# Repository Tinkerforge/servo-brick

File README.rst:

Servo Brick
===========

This repository contains the firmware source code and the hardware design
files. The documentation generator configs can be found at
https://github.com/Tinkerforge/generators

Repository Content
------------------

software/:
 * examples/: Examples for all supported languages
 * build/: Compiled files
 * src/: Source code of firmware
 * Makefile: Makefile to build project

hardware/:
 * Contains KiCad project files and additionally schematics as PDF

datasheets/:
 * Contains datasheets for sensors and complex ICs that are used

Hardware
--------

The hardware is designed with the open source EDA Suite KiCad
(http://www.kicad.org). Before you are able to open the files,
you have to install the Tinkerforge kicad-libraries
(https://github.com/Tinkerforge/kicad-libraries). You can either clone
them directly in hardware/ or clone them in a separate folder and
symlink them into hardware/
(ln -s kicad_path/kicad-libraries project_path/hardware). After that you
can open the .pro file in hardware/ with KiCad and from there view and
modify the schematics and the PCB layout.

Software
--------

If you want to do your own Brick/Bricklet firmware development we highly
recommend that you use our build environment setup script and read the
tutorial (https://www.tinkerforge.com/en/doc/Tutorials/Tutorial_Build_Environment/Tutorial.html).

To compile the C code we recommend you to install the newest GNU Arm Embedded
Toolchain (https://launchpad.net/gcc-arm-embedded/+download).
You also need to install bricklib (https://github.com/Tinkerforge/bricklib).

You can either clone it directly in software/src/ or clone it in a
separate folder and symlink it into software/src/
(ln -s bricklib_path/bricklib project_path/software/src/). Finally make sure to
have CMake installed (http://www.cmake.org/cmake/resources/software.html).

After that you can build the firmware by invoking make in software/.
The firmware (.bin) can then be found in software/build/ and uploaded
with brickv (click button "Flashing" on start screen).

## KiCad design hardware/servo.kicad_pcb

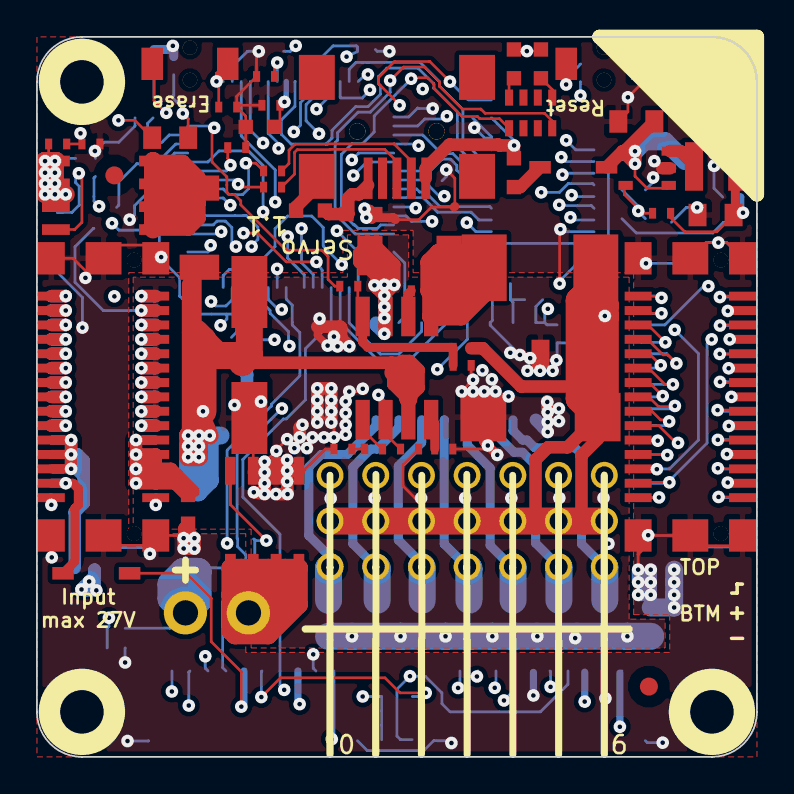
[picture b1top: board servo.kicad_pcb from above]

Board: 4 copper layers, 40.0 x 40.0 mm, 113 parts (0 on the bottom side), 116 nets.

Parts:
C1, C2: 9pF; C0402
C3: 100µF; 3528-21
C4, C6: 10µF; C0805
C5, C8, C9, C10, C12, C13, C15, C16, C18, C20, C21, C27, C28, C32: 100nF; C0402
C7, C19: 4.7µF; C0603
C11: 2.2µF; C0603
C14: DNP; C0402
C17: 10µF/10V; C0805
C22: 220µF/35V; ELKO_83
C23: 10µF/35V; C1206
C24, C30: 100nF; C0603
C25: 1µF/10V; C0402
C26: 1nF; C0402
C29: 1µF/10V; 0402
C31: 47µF/10V; C1206
C33: 470µF/10V; 7343
D1: blue; D0603
D2: red; D0603
D3, D5: B0520LW-7-F; SOD-123
D4: Z3.3V; SOD-123
D6: Z12V; SOD-123
D7, D8, D9: PMEG4050BEP; SOD-128
FB1, FB2, FB3, FB4, FB5: FB; C0603
Fiducial_Mark: VAL**; Fiducial_Mark
Fiducial_Mark#2, Fiducial_Mark#3, Fiducial_Mark#4: VAL**; Fiducial_Mark
J1, J2, J3, J4: DRILL; DRILL_NP
J5: USB-MINI-B-SMD
J6, J8: STACK-UP-HIGH; BTB08-ACS-TOP
J7, J9: STACK-DOWN; BTB08-ACS-BTM
J10: CON-SERVO; CON-Servo
L1: NR3015T4R7M; NR3030
L2: LBR2012T100K; C0805
L3: 10µH; SRP7030
P1, P2: CON-SENSOR
P3: black; OQ_2P
Q1: FDS8449; SOIC-8-MOSFET
Q2: AO4421; SOIC-8-MOSFET
Q3: 2N7002; SOT23GDS
R1, R2: 27; R0402
R3: 1.8k; R0402
R4: 2.7k; R0402
R5: 0; R0603
R6: DNP; R0603
R7: 1R0; R0402
R8, R11, R15, R18, R23: 1k; R0402
R9: FB; C0603
R10, R13, R14, R16, R17, R20, R21, R22: 10k; R0402
R12, R19: 100k; R0402
R24, R25, R26, R27, R28, R29, R30: 0R1; R0805
RP1, RP2: 1k; 4X0603
Ref**: Val**; Logo_31x31m
SW1: Reset; TACT-SWITCH
SW2: Erase; TACT-SWITCH
U1: AT91SAM3SXB; LQFP64
U2: EUP3406; SOT23-5
U3: AOZ1212; SO-8
U4: 74HC245; TSSOP20
U5: MCP3008; SOIC16
VAL: CE_5mm
VAL#2: WEEE_7mm
X1: 16Mhz; CRYSTAL_3225

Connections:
3V3: C4.1, C5.1, C7.1, C8.1, C9.1, C10.1, C14.1, C17.1, C18.1, C21.1, C29.1, D1.1, D2.1, D4.2, D5.1, J6.20, L1.2, P1.3, P1.6, P2.3, R5.1, R22.2, RP2.1, RP2.2, RP2.3, RP2.4, SW2.2, U1.1, U1.7, U1.18, U1.45, U1.58, U5.16
BRICKLET-I2C-SCL: P1.4, P2.4, RP2.5, U1.36
BRICKLET-I2C-SDA: P1.5, P2.5, RP2.8, U1.43
BRICKLET-IO0_0/AD0: P1.7, U1.3
BRICKLET-IO0_1/DA0: P1.8, U1.59
BRICKLET-IO0_2/PWM0: P1.9, U1.20
BRICKLET-IO0_3: P1.10, U1.41
BRICKLET-IO1_0/AD1: P2.7, U1.4
BRICKLET-IO1_1: P2.8, U1.6
BRICKLET-IO1_2/PWM1: P2.9, U1.42
BRICKLET-IO1_3: P2.10, U1.47
CUR-SERVO-0: J10.A1, R24.1, U5.8
CUR-SERVO-1: J10.B1, R25.1, U5.7
CUR-SERVO-2: J10.C1, R26.1, U5.6
CUR-SERVO-3: J10.D1, R27.1, U5.5
CUR-SERVO-4: J10.E1, R28.1, U5.4
CUR-SERVO-5: J10.F1, R29.1, U5.3
CUR-SERVO-6: J10.G1, R30.1, U5.2
GND: C1.2, C2.2, C3.2, C4.2, C5.2, C6.2, C7.2, C8.2, C9.2, C10.2, C11.2, C12.2, C13.2, C15.2, C16.2, C17.2, C18.2, C19.2, C20.2, C21.2, C32.2, D4.1, FB1.1, FB4.2, J6.EP, J7.EP, J8.EP, J9.EP, P1.2, P1.EP, P2.2, P2.6, P2.EP, R4.1, R6.2, R9.2, R11.1, R15.1, R18.1, SW1.2, U1.2, U1.17, U1.46, U1.60, U2.2, U4.9, U4.10, U4.19, X1.3
unnamed: C11.1, C12.1, C13.1, C15.1, C16.1, L2.1, U1.8, U1.12, U1.24, U1.54
unnamed: C14.2, R5.2, R6.1, U2.5
unnamed: C19.1, R7.1
unnamed: C20.1, L2.2, R7.2, U1.64
unnamed: C22.1, C23.1, C24.1, D7.2, D8.2, U3.7
unnamed: C25.1, U3.8
unnamed: C26.1, R17.1
unnamed: C27.1, D9.2, L3.1, U3.1
unnamed: C27.2, U3.2
unnamed: C28.2, R22.1, R23.2, U5.15
unnamed: D1.2, RP1.8
unnamed: D2.2, RP1.5
unnamed: D5.2, J8.28, J9.28
unnamed: D6.2, Q1.G, R12.2
unnamed: D7.1, P3.1, R12.1, R14.2
unnamed: D8.1, Q2.D
unnamed: FB1.2, FB2.1, J5.5
unnamed: FB2.2, J5.6
unnamed: FB3.2, J5.1, R3.1
unnamed: FB4.1, J8.21, J8.23, J8.25, J8.27, J9.21, J9.23, J9.25, J9.27
unnamed: FB5.2, J8.22, J8.24, J8.26, J9.22, J9.24, J9.26
unnamed: J5.2, R1.1
unnamed: J5.3, R2.1
unnamed: J6.6, J7.8
unnamed: J6.7, J7.7, R8.1
unnamed: J6.8, J7.10
unnamed: J6.10, J7.12
unnamed: J6.12, J7.14
unnamed: J6.13, J7.13
unnamed: J6.14, J7.16
unnamed: J6.15, J7.15
unnamed: J6.16, J7.18
unnamed: J6.17, J7.17
unnamed: J6.18, J7.20
unnamed: J6.21, J7.21
unnamed: J6.22, J7.22
unnamed: J6.23, J7.23
unnamed: J6.24, J7.24
unnamed: J6.25, J7.25
unnamed: J6.27, J7.27
unnamed: J6.29, J7.29
unnamed: J6.30, J7.30
unnamed: J8.29, J9.29
unnamed: J8.30, J9.30
unnamed: J10.A3, U4.12
unnamed: J10.B3, U4.13
unnamed: J10.C3, U4.14
unnamed: J10.D3, U4.15
unnamed: J10.E3, U4.16
unnamed: J10.F3, U4.17
unnamed: J10.G3, U4.18
unnamed: L1.1, U2.3
unnamed: P3.2, Q1.D
unnamed: Q2.G, Q3.D, R13.2
unnamed: R1.2, U1.56
unnamed: R2.2, U1.57
unnamed: R17.2, U3.5
unnamed: R19.2, R20.1, R21.2, U3.4
unnamed: RP1.1, U1.30
unnamed: RP1.4, U1.29
unnamed: SW2.1, U1.55
PWM-SERVO-0: U1.48, U4.2
PWM-SERVO-1: U1.26, U4.3
PWM-SERVO-2: U1.25, U4.4
PWM-SERVO-3: U1.23, U4.5
PWM-SERVO-4: U1.19, U4.6
PWM-SERVO-5: U1.9, U4.7
PWM-SERVO-6: U1.15, U4.8
PWR-AD-CLK: U1.44, U5.13
PWR-AD-CS: U1.32, U5.10
PWR-AD-MISO: U1.35, U5.12
PWR-AD-MOSI: U1.34, U5.11
PWR-ENABLE: R16.2, U1.16, U3.6
PWR-SET-VOLTAGE: R21.1, U1.63
PWR-VEXT: R14.1, R15.2, U1.10
PWR-VSTACK: R10.1, R11.2, U1.13
PWR-VSTACK-SW: Q3.G, R18.2, U1.37
STACK-DETECT/JTAG-TMS: J6.9, J7.9, U1.51
STACK-I2C-SCL/JTAG-TDO: J6.4, J7.4, U1.49
STACK-I2C-SDA/JTAG-TDI: J6.2, J7.2, U1.33
STACK-INT: J6.19, J7.19, U1.52
STACK-PGND: C22.2, C23.2, C24.2, C25.2, C26.2, C28.1, C29.2, C30.2, C31.2, C33.2, D6.1, D9.1, J8.1, J8.3, J8.5, J8.7, J8.9, J8.11, J8.13, J8.15, J8.17, J8.19, J9.1, J9.3, J9.5, J9.7, J9.9, J9.11, J9.13, J9.15, J9.17, J9.19, Q1.S, Q3.S, R9.1, R16.1, R20.2, R23.1, R24.2, R25.2, R26.2, R27.2, R28.2, R29.2, R30.2, U3.3, U5.1, U5.9, U5.14
STACK-PVCC: J8.2, J8.4, J8.6, J8.8, J8.10, J8.12, J8.14, J8.16, J8.18, J8.20, J9.2, J9.4, J9.6, J9.8, J9.10, J9.12, J9.14, J9.16, J9.18, J9.20, Q2.S, R10.2, R13.1
STACK-RESET: R8.2, SW1.1, U1.39
STACK-SER-RXD: J6.26, J7.26, U1.11
STACK-SER-TXD: J6.28, J7.28, U1.14
STACK-SPI-MISO: J6.1, J7.1, U1.27
STACK-SPI-MOSI: J6.3, J7.3, U1.22
STACK-SPI-SCLK: J6.5, J7.5, U1.21
STACK-SPI-SELECT: J7.6, U1.28
STACK-SYNC/JTAG-TCK: J6.11, J7.11, U1.53
USB-DETECT: R3.2, R4.2, U1.38
VPP: C30.1, C31.1, C33.1, J10.A2, J10.B2, J10.C2, J10.D2, J10.E2, J10.F2, J10.G2, L3.2, R19.1
VSTACK: C3.1, C6.1, C32.1, D3.2, FB5.1, P1.1, P2.1, U2.1, U2.4, U4.1, U4.20
VUSB: D3.1, FB3.1
XIN: C2.1, U1.62, X1.2
XOUT: C1.1, U1.61, X1.1

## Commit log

2011-08-25 initial hardware source commit
2011-08-25 add project description
2011-08-25 change voltage epsilon from 200 to 1000mV
2011-08-25 fix missing parameters in debug messages
2011-08-26 remove adc conversion in tick task, bricklib uses freerun now
2011-08-26 change diode PMEG1020EH -> B0520LW-7-F
2011-08-31 fix typo in example
2011-09-06 add red led error status code
2011-09-08 use voltage epsilon to change between external and stack voltage
2011-09-08 compare external voltage for switching between external and stack voltage
2011-09-08 adapt servo numbering according to hardware numbering
2011-09-08 adapt servo numbering: current measurement was missing, now adapted
2011-09-13 remove unnecessary newline
2011-09-13 add java bindings and examples
2011-09-14 limit line length of java examples to 100 characters
2011-09-15 fix copy and paste fail in java example comments
2011-09-26 Add C# examples and bindings
2011-10-05 Remove Bindings and IP Connection (these are generated and they change too often) and rename bindings to examples
2011-10-05 add tinkerforge package to python imports
2011-10-06 remove faulty gcc commandline invocation
2011-10-06 add firmware version and name
2011-11-09 only send reached signals if buffer empty (otherwise wait 1ms for next tick)
2011-11-24 set servo position once at startup
2012-02-13 No major changes - add fiducials on board - add revision on schematics
2012-02-14 add compatability for different tick types
2012-02-15 Add changelog
2012-03-05 Fix bug with timeouts on windows (through bricklib)
2012-03-11 Fix bug with ADC calibration readout (through bricklib)
2012-04-25 Unify capitalization of "IP connection" in examples
2012-05-09 Add PHP examples
2012-05-14 java: Remove unnecessary new String(...) calls
2012-05-25 Add Ruby examples
2012-06-05 Fix register_callback syntax error in Ruby examples on Windows
2012-06-12 Prefer IPConnection destroy over join_thread
2012-06-29 Add get_temperature and reset function (through bricklib)
2012-07-01 Add generate_makefile.bat for windows
2012-07-02 update to newest cmsis core_m3 files (through bricklib)
2012-07-02 Add support for minimum period of 1us and add usb hotplug support
2012-07-25 Add Delphi examples
2012-08-08 delphi: Add comment about UID
2012-09-07 Ignore temporary build files
2012-10-08 Fix typo in changelog
2012-10-10 Remove unused define
2012-10-17 Add hardware name for compatibility with new bricklib
2012-10-26 Change Bricklet Context size from 250 to 256 (through bricklib)
2012-10-26 Fix revision
2012-11-13 Support for protocol 2.0
2012-11-22 Add compatability to newest bricklib version
2012-11-22 Reenumerate after USB reconnect
2012-11-29 Make Python examples compatible to Protocol V2.0
2012-11-29 Make Ruby examples Protocol 2.0 compatible
2012-11-29 Make C examples Protocol 2.0 compatible
2012-11-29 Make Java examples Protocol 2.0 compatible
2012-11-29 Make PHP examples Protocol 2.0 compatible
2012-11-29 Make Delphi/Pascal examples Protocol 2.0 compatible
2012-11-30 Add invalid parameter checks for servo_num parameter
2012-11-30 Fix invalid parameter checks
2012-11-30 delphi: Remove unnecessary parentheses and call destructor again
2012-12-05 Add protocol 2.0 compatability to C# bindings
2012-12-06 Fix C example
2012-12-07 Fix Java example
2012-12-11 Avoid g++ warnings about missing casts in C examples
2012-12-13 Use user data parameter in PHP example
2013-01-09 Use specific device object for callbacks
2013-01-14 Adapt Java examples to latest IP Connection API
2013-01-16 Update Java example and use a final local instead of a global static variable
2013-01-17 Make Java examples compatible to new listener approach
2013-02-07 Use IPconnection disconnect explicitly in examples
2013-02-18 Add Visual Basic .NET examples
2013-02-22 Update Java example
2013-03-27 Add enable/disable API for reached callbacks
2013-03-27 Add changelog for 2.0.1
2013-04-11 Add watchdog timer (restart after 16s of "deadlock")
2013-06-17 Add missing defines for enable/disable API for reached callbacks
2013-06-18 Add missing enable_position_reached_callback to examples
2013-06-27 Use tick_task to detect usb connect/disconnect instead of interrupt (through bricklib)
2013-08-13 Add shell examples
2013-08-13 shell: Remove debug options
2013-08-16 shell: Remove debug output
2013-08-21 windows: Don't trigger a build in generate_makefile.bat
    Also use normal make instead of a special named one.
2014-01-08 delphi: Remove empty parentheses
2014-01-10 Add Perl examples
2014-01-14 perl: Fix warning about unsharing the $servo variable
2014-01-15 php: Use const for constant values
2014-02-07 Fix typo
2014-02-07 Add Mathematica examples
2014-02-10 perl: fixed namespace
2014-02-11 javascript: adding examples
2014-02-11 javascript: short examples
2014-02-18 javascript: examples fixed
2014-02-20 javascript: adding html exmaples
2014-02-20 javascript: fixed title on the page
2014-02-24 javascript: port 4280, startExample()
2014-02-25 Add PWM example in C
2014-02-28 javascript: Break long lines and cleanup whitespace
2014-03-05 Add LabVIEW examples
2014-03-06 labview: Add examples in LV2010 format
2014-03-25 matlab: adding examples
2014-04-02 java: Unify constants style
2014-04-02 perl: Unify print style
2014-04-17 matlab: Adapt examples to new callback style
2014-04-17 matlab: Add parentheses to make pygments happy
2014-06-12 change voltage divider values
2014-07-04 Add support SPI DMA (currently turned off by default)
2014-07-07 Remove USB hotplug support (through bricklib)
2014-07-15 java: Replace System.console() usage with an Eclipse compatible pattern
2014-11-25 Use new SPI protocol
2014-11-25 Add changelog for v2.3.0
2014-12-02 Use ReadLine instead of ReadKey for C# example
2015-02-13 vbnet: Use ReadLine instead of ReadKey
    Because ReadKey doesn't work with a pipe as stdin on the RED Brick.
2015-03-02 windows: Stop cmake from searching for mingw32-make.exe
    Using MinGW Makefiles as generator makes cmake search for mingw32-make.exe
    which might not be installed because GnuWin32's make.exe is used instead.
2015-04-09 c: Whitespace
2015-06-24 javascript: Clean up output creation
2015-06-29 octave: Handle short difference between Octave 3.6 and 3.8
    In Octave 3.6 a short is not automatically handled as a number.
2015-07-25 Make JavaScript browser example textarea readonly
2015-07-28 Cleanup C/C++, C#, Java, Python and Ruby examples
2015-07-28 Simplify variable names in examples again
2015-07-29 Reformat changelog
2015-07-30 Cleanup C/C++, C#, Java, Python and Ruby configuration examples
2015-08-07 Use full device class name in Python examples
2015-08-12 Fix minor warnings in C/C++ examples
2015-08-14 Cleanup Delphi examples
2015-08-18 Add missing disable call in PWM example
2015-08-18 Cleanup VB.NET examples
2015-08-19 Cleanup Perl examples
2015-09-09 Duplicate cmake call to fix bug during cmake creation
2015-09-30 Generator based example cleanup
2015-11-12 matlab: Fix callback handling for R2014a
    http://undocumentedmatlab.com/blog/matlab-callbacks-for-java-events-in-r2014a
2015-11-25 Include date and commit into changelog
2015-11-30 vbnet: Shorten long line
2016-05-18 c: Add missing device destroy call
2016-07-01 Make the change UID comment more explicit
2016-08-29 Make sure to use all chunks when writing firmware
    Change through Bricklib
2016-08-29 Fix changelog date
2016-12-02 Add missing source includes for newest bricklib version
2017-01-06 Add COM_MESSAGE_USER_LAST_FID define (needed for newest bricklib)
2017-04-13 csharp: Adapt example
2017-05-11 Add support for co-mcu Bricklets
2017-05-11 Add ref for last changelog entry
2017-06-02 octave: Use javaObject instead of deprecated java_new
2017-06-02 java: Whitespace
2017-06-02 csharp,vbnet: Remove unnecessary System prefix
2017-06-28 Update changelog and version
2017-06-28 Add tag ref to changelog
2017-06-30 Add 3d information (tbc); fix direction of some diodes
2017-07-07 Add 3d information (final)
2017-07-07 Servo Brick: Add 3d model (*.step & *.FCStd)
2017-08-01 Add 3d component: NR3030
2017-09-12 Add example for PWM Generator (Java)
2017-09-12 Remove package
2017-09-13 Fix indentation
2017-09-13 java: Fix mismatch between PWM example classname and filename
2017-09-13 java: Make PWM example make the C/C++ example match more closely
2017-11-30 Update examples from generator
2017-12-05 Remove initial USB enumeration (now done in bricklib)
2017-12-05 Increase firmware version, update changelog
2017-12-07 mathematica: Also generate .nb files
2017-12-12 Remove unused include
2017-12-12 Remove unused variable
2017-12-13 Add date and ref to changelog
2018-01-11 Increase version number (message duplication bug fix through bricklib)
2018-01-11 Add ref to changelog
2018-02-19 javascript: Close div tag correctly
2018-02-20 Cleanup KiCad libraries config
    Ensure LibDir=kicad-libraries and LibName1=tinkerforge.
    Remove special library.
2018-04-27 Update version and changelog
2018-04-27 Add git ref to changelog
2018-05-24 perl: Use strict in examples
2018-07-11 Add Makefile with docker support
2018-07-11 Update directory structure and build instructions
2018-07-11 Remove obsolete generate_makefile scripts
2018-07-25 Add new 3d model
2018-07-31 Increase version and update changelog
2018-07-31 Update changelog ref
2018-09-03 Unify spelling in changelog
2018-11-06 Add rust examples
2018-11-07 rust: Accept host names for ip connection, fix naming inconsistencies
2018-11-07 rust: Rename callback receivers.
2018-12-14 Add go examples.
2018-12-18 go: Change import path.
2018-12-18 go: Change import path again.
2018-12-20 rust: Reformat examples.
2019-01-24 mqtt: Add examples.
2019-01-24 mqtt: Fix example header.
2019-01-24 mqtt: Remove executable bit in example permissions.
2019-01-24 go: Minor example fixes.
2019-01-24 mqtt: Minor example fixes.
2019-02-27 Increase version for new release (changes in bricklib)
2019-02-27 Add rev to changelog
2019-08-22 c: Adapt to bindings changes
2019-11-22 Make sure that Servo Brick output goes low if pulse width and position is set to 0.
2019-11-22 Add ref for 2.3.9
2020-01-13 examples: Use python3 input instead of python2 raw_input.
2020-01-13 examples: mqtt: Remove trailing whitespace.
2020-01-14 examples: Use python3 input by default.
2020-02-26 c: Update "Change UID" comment style
2020-03-18 Whitespace
2020-03-18 rust: Update to new skeleton
2020-04-07 examples: rust: Always block when calling bindings functions.
2021-01-14 mqtt: Fix typo
2021-01-14 rust: Break long comment
2021-10-25 Update KiCad link
    https://www.kicad.org/blog/2021/10/Avoid-links-to-former-kicad-domain/
2022-07-06 Add license files.

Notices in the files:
hardware/servo.kicad_pcb:
Licensed under CERN OHL v.1.1
Copyright (©) 2013, B.Nordmeyer
Copyright Tinkerforge GmbH 2013.
This documentation describes Open Hardware and is licensed under the
CERN OHL v. 1.1.
